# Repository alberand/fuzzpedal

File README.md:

This repository contains a lot of information on how to build a Fuzz Pedal based
on well-known Big Muff PI pedal.

## Demo Reconds

[][4] 

[][5] 

[][6] 

### Schematics

### PCB dimensions

### 3D Render of PCB

### Photo of PCB

### Photo of assembled pedal

## TODO

* Add [rubber feets][1] (After discussion seems to be unnecessary and it's better to have Hook-and-loop fastener)
* Write article on how to paint Aluminum case
* Add template for drilling holes (A4 paper with holes)
* Update BOM (better caps, better LED holder)  - in progress
* Try screen print on the case
* Describe screen printing process
* Find what to use as a final coat for case painting

## Cost

Here is crude cost calculation of one Pedal. Remember that this doesn't include
any tools. The shipping price could vary (in my case I had many more parcels
😕). In total one pedal cost about 50 - 60 💶 euro (without shipping) + you would
have a few paint sprays.

| Material Type                | Quantity       | Price [EUR] |
|------------------------------|----------------|-------------|
| PCB                          | 5 (min amount) |     8.5     |
| Electronic components & Misc |      1 set     |      25     |
| Case                         |        1       |      11     |
| Ground & Color & Clear Paint |        3       |     6x3     |
| Shipping                     |       ~4       |     20x4    |

How long does it take to make a pedal? If you have any experience in soldering,
painting it will take somewhere around 33 hours mainly due waiting for paint to
dry.

| Activity Type             | Time [hours] |
|---------------------------|--------------|
| Board Soldering           |       5      |
| Case drilling             |       2      |
| Case cleaning & polishing |      0.5     |
| Case painting             |      25      |
| Assembling                |      0.5     |

## Assembling process

TODO In progress

The assebmly process is quite simple. The most time-consuming part is PCB
soldering. Otherwise, you just need to put PCB into box.

### Order components & PCB

1. Import BOM to Mouser or Farnell and order components. The BOM is prepared for
   those to distributors. However, sometimes components aren't in stock and it
   can take months for them to restock them.
2. Order the rest of the components from Aliexpress - enclosure and foot switch.
   Those parts are also available on Amazon. I would recommend to by foot switch
   from amazon as it seems to be in better quality. The case could be also
   ordered from Mouser or Farnell.
3. Import Gerber files to PCB manufacturer and order PCBs. I used jlcpcb.com
   which worked out quite well.

### Solder board

1. TODO image of the component placement (print it)
2. I recommend soldering components in the following order:
    1. Resistors
    2. Electrolytic Capacitors (those with polarity)
    3. Capacitor
    4. Transistors
    5. Diodes
    6. Thermal fuse (yellow)
    7. Potentiometers, Jacks and Switch
    8. Wires between PCBs
3. Prepare wires, LED with wires and power jack with wires
4. Solder wires to LED and to the Power jack, but don't solder it to the board
   yet. Also, don't forget to put heat shrink tubes.
5. Solder the LED to the board 

### Enclosure processing

TODO describe what instruments to use
1. Print the template for the hole placement (TODO not in the repo)
2. Cut the template and attach it to the case with adhesive tape
3. Drill the holes
4. Remove the template and polish the case with different sandpapers (TODO add
   sizes)
5. Paint the case (read the instruction on the spray):
    1. 2 layers of primer
    2. 2 layers of color paint
    3. 1 layers of protection layer
6. Screen printing (TODO)

### Assemble the pedal

1. Break the board
2. Put the LED into the case and screw it to the case
3. Screw switch and jacks
4. Put second board into the enclosure and screw the knobs
5. Put power jack into the enclosure
6. Solder power jack wires to the board
7. Use thermal glue (TODO it doesn't work) to fix the board inside the case
8. Screw the bottom of the enclosure

### References

* [ElectroSmash - Big Muff PI analysis](https://www.electrosmash.com/big-muff-pi-analysis)
* [How to "Screen printing"](https://www.youtube.com/watch?v=NS8Q9LUIKA8)

[1]: http://www.diyguitarpedals.com.au/shop/index.php?main_page=product_info&cPath=15&products_id=591
[2]: http://www.caravanelectroworks.com/?p=418
[3]: http://rezzonics.blogspot.com/2018/05/nutube-screamer-schematics-bom-layout.html
[4]: https://soundcloud.com/user-605705068/fuzzpedal-demo-param-1
[5]: https://soundcloud.com/user-605705068/fuzzpedal-demo-param-2
[6]: https://soundcloud.com/user-605705068/fuzzpedal-demo-param-3

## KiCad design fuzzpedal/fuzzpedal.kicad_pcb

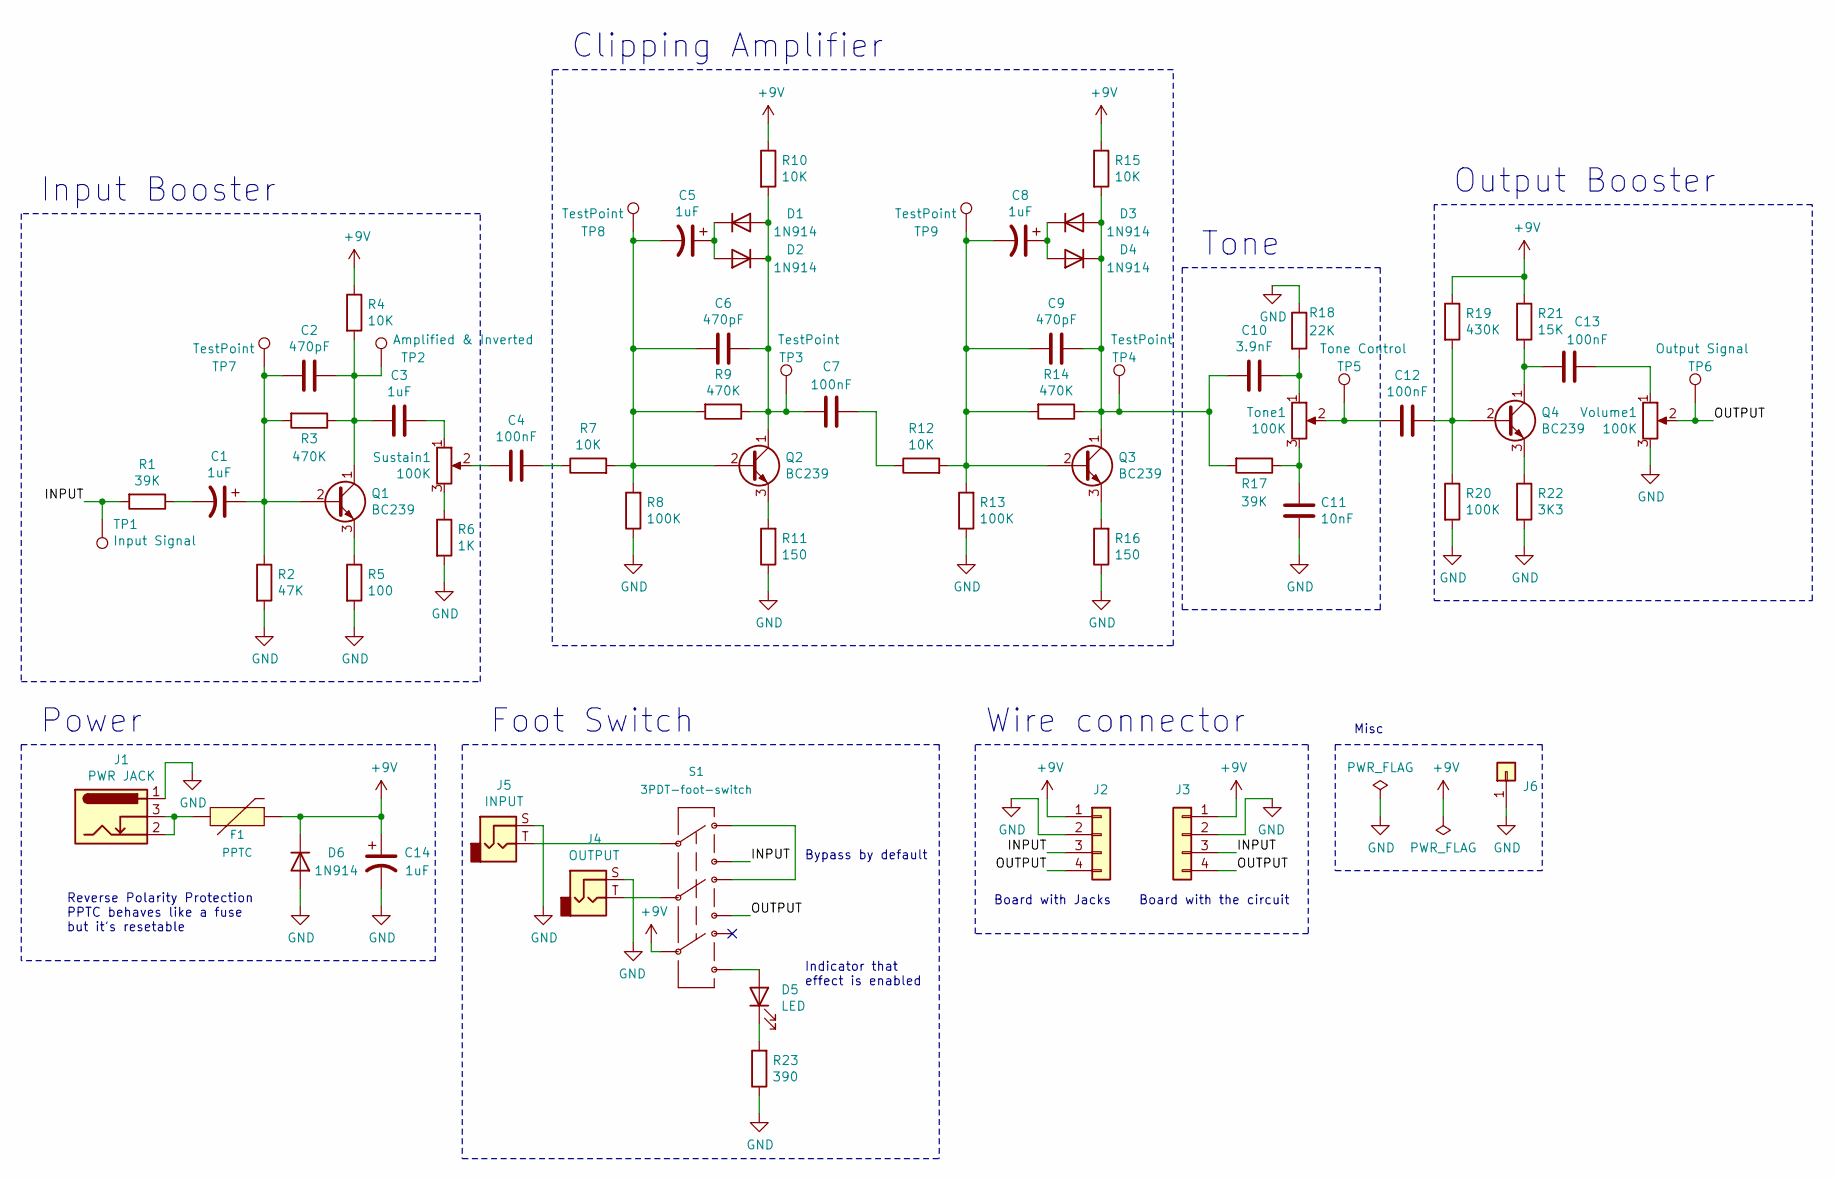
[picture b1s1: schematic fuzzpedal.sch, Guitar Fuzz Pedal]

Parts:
C1, C5, C8, C14: 1uF; CP_Radial_D5.0mm_P2.00mm; Mouser 710-860020672005
C2, C6, C9: 470pF; C_Rect_L7.2mm_W4.5mm_P5.00mm_FKS2_FKP2_MKS2_MKP2; Mouser 505-FKP2D004701DKSSD
C3: 1uF; C_Rect_L7.2mm_W5.5mm_P5.00mm_FKS2_FKP2_MKS2_MKP2; Mouser 505-MKS2C041001FKI00
C4, C7, C12, C13: 100nF; C_Rect_L7.2mm_W2.5mm_P5.00mm_FKS2_FKP2_MKS2_MKP2; Mouser 871-B32529C104K000
C10: 3.9nF; C_Rect_L7.2mm_W4.5mm_P5.00mm_FKS2_FKP2_MKS2_MKP2; Mouser 505-FKP2C013901DHC00
C11: 10nF; C_Rect_L7.2mm_W5.5mm_P5.00mm_FKS2_FKP2_MKS2_MKP2; Mouser 505-FKP2C021001G00KS
D1, D2, D3, D4, D6: 1N914; D_DO-35_SOD27_P7.62mm_Horizontal; LCSC C125665
D5: LED; LED_D5.0mm; LCSC C162069
F1: PPTC; C_Disc_D8.0mm_W2.5mm_P5.00mm; Mouser 652-MF-R020
J1: PWR JACK; PinHeader_1x03_P2.54mm_Vertical
J2: Wire connector (smol); PinHeader_1x04_P2.54mm_Vertical
J3: Wire connector (circuit); PinHeader_1x04_P2.54mm_Vertical
J4: OUTPUT; NMJ6HC-S; Mouser 568-NMJ4HC-S
J5: INPUT; NMJ6HC-S; Mouser 568-NMJ4HC-S
J6: GND for scope; PinHeader_1x01_P2.54mm_Vertical
Q1, Q2, Q3, Q4: BC239; TO-92L_Inline_Wide; Mouser 512-BC549CTA
R1, R17: 39K; R_Axial_DIN0207_L6.3mm_D2.5mm_P10.16mm_Horizontal; Mouser 603-CFR-12JB-52-39K
R2: 47K; R_Axial_DIN0207_L6.3mm_D2.5mm_P10.16mm_Horizontal; Mouser 603-CFR-12JB-52-47K
R3, R9, R14: 470K; R_Axial_DIN0207_L6.3mm_D2.5mm_P10.16mm_Horizontal; Mouser 603-CFR-12JT-52-470K
R4, R7, R10, R12, R15: 10K; R_Axial_DIN0207_L6.3mm_D2.5mm_P10.16mm_Horizontal; Mouser 603-CFR-12JT-52-10K
R5: 100; R_Axial_DIN0207_L6.3mm_D2.5mm_P10.16mm_Horizontal; Mouser 603-CFR-12JT-52-100R
R6: 1K; R_Axial_DIN0207_L6.3mm_D2.5mm_P10.16mm_Horizontal; Mouser 603-CFR-12JT-52-1K
R8, R13, R20: 100K; R_Axial_DIN0207_L6.3mm_D2.5mm_P10.16mm_Horizontal; Mouser 603-CFR-12JR-52-100K
R11, R16: 150; R_Axial_DIN0207_L6.3mm_D2.5mm_P10.16mm_Horizontal; Mouser 603-CFR-12JT-52-150R
R18: 22K; R_Axial_DIN0207_L6.3mm_D2.5mm_P10.16mm_Horizontal; Mouser 603-CFR-12JT-52-22K
R19: 430K; R_Axial_DIN0207_L6.3mm_D2.5mm_P10.16mm_Horizontal; Mouser 603-CFR-12JB-52-430K
R21: 15K; R_Axial_DIN0207_L6.3mm_D2.5mm_P10.16mm_Horizontal; Mouser 603-CFR-12JT-52-15K
R22: 3K3; R_Axial_DIN0207_L6.3mm_D2.5mm_P10.16mm_Horizontal; Mouser 603-CFR-12JR-52-3K3
R23: 390; R_Axial_DIN0207_L6.3mm_D2.5mm_P10.16mm_Horizontal; Mouser 603-CFR-12JB-52-390R
S1: 3PDT-foot-switch; SF17020F-0302-21R-L; Mouser 107-SF17020F-32-21RL
Sustain1: 100K; Potentiometer_Alps_RK09K_Single_Vertical; Mouser 688-RK09D113BF25B15
TP1: Input Signal; TestPoint_Pad_2.0x2.0mm
TP2: Amplified & Inverted; TestPoint_Pad_2.0x2.0mm
TP3, TP4, TP7, TP8, TP9: TestPoint; TestPoint_Pad_2.0x2.0mm
TP5: Tone Control; TestPoint_Pad_2.0x2.0mm
TP6: Output Signal; TestPoint_Pad_2.0x2.0mm
Tone1: 100K; Potentiometer_Alps_RK09K_Single_Vertical; Mouser 688-RK09D113BF25B15
Volume1: 100K; Potentiometer_Alps_RK09K_Single_Vertical; Mouser 688-RK09D113BF25B15

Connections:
+9V: C14.1, D6.1 (K), F1.2, J2.1, J3.1, R4.1, R10.1, R15.1, R19.1, R21.1, S1.8
/INPUT: J2.3, J3.3, R1.2, S1.3, TP1.1
/OUTPUT: J2.4, J3.4, S1.6, TP6.1, Volume1.2
GND: C11.2, C14.2, D6.2 (A), J1.1, J2.2, J3.2, J4.S, J5.S, J6.1, R2.2, R5.2, R6.2, R8.1, R11.1, R13.1, R16.1, R18.1, R20.2, R22.2, R23.1, Volume1.3; also elsewhere on the board
unnamed: C1.1, C2.2, Q1.2 (B), R2.1, R3.2, TP7.1
unnamed: C1.2, R1.1
unnamed: C2.1, C3.2, Q1.1 (C), R3.1, R4.2, TP2.1
unnamed: C3.1, Sustain1.1
unnamed: C4.1, R7.1
unnamed: C4.2, Sustain1.2
unnamed: C5.1, D1.1 (K), D2.2 (A)
unnamed: C5.2, C6.2, Q2.2 (B), R7.2, R8.2, R9.2, TP8.1
unnamed: C6.1, C7.2, D1.2 (A), D2.1 (K), Q2.1 (C), R9.1, R10.2, TP3.1
unnamed: C7.1, R12.1
unnamed: C8.1, D3.1 (K), D4.2 (A)
unnamed: C8.2, C9.2, Q3.2 (B), R12.2, R13.2, R14.2, TP9.1
unnamed: C10.1, R18.2, Tone1.1
unnamed: C9.1, C10.2, D3.2 (A), D4.1 (K), Q3.1 (C), R14.1, R15.2, R17.2, TP4.1
unnamed: C11.1, R17.1, Tone1.3
unnamed: C12.1, Q4.2 (B), R19.2, R20.1
unnamed: C12.2, TP5.1, Tone1.2
unnamed: C13.1, Volume1.1
unnamed: C13.2, Q4.1 (C), R21.2
unnamed: D5.1 (K), R23.2
unnamed: D5.2 (A), S1.9
unnamed: F1.1, J1.2, J1.3
unnamed 26: J4.T, S1.5; also elsewhere on the board
unnamed 27: J5.T, S1.2; also elsewhere on the board
unnamed: Q1.3 (E), R5.1
unnamed: Q2.3 (E), R11.2
unnamed: Q3.3 (E), R16.2
unnamed: Q4.3 (E), R22.1
unnamed: R6.1, Sustain1.3
unnamed: S1.1, S1.4

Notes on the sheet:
Input Booster
Clipping Amplifier
Tone
Output Booster
Bypass by default
Foot Switch
Power
Indicator that effect is enabled
Misc
Reverse Polarity Protection PPTC behaves like a fuse but it's resetable
Board with the circuit
Board with Jacks
Wire connector

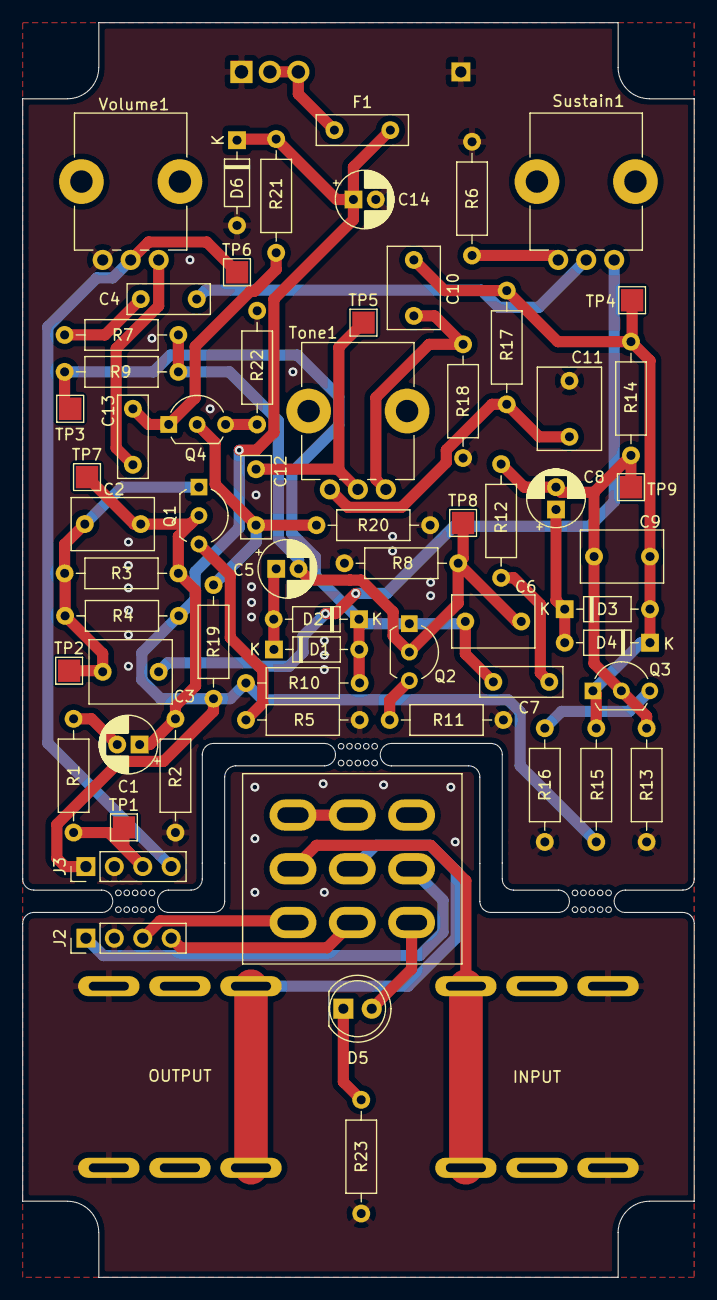
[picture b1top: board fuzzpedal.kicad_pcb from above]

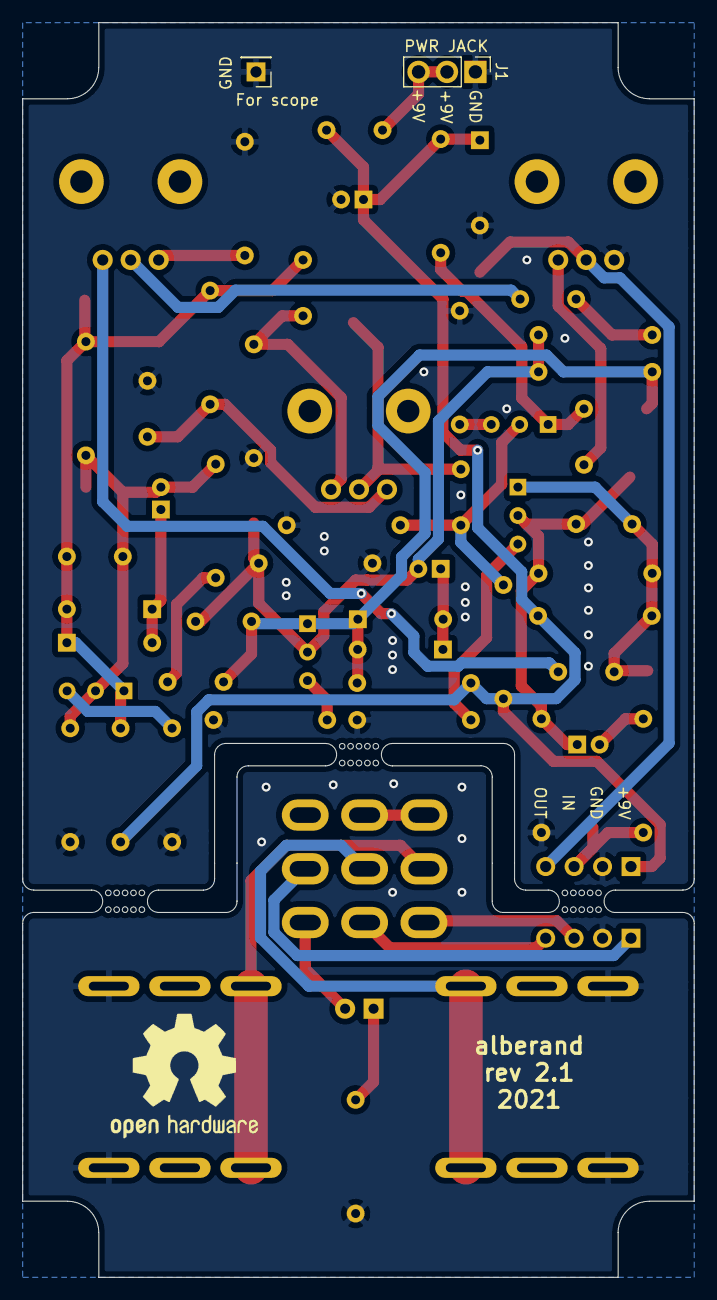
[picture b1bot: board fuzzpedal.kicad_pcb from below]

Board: 2 copper layers, 60.0 x 112.1 mm, 70 parts (2 on the bottom side), 34 nets.

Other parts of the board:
INPUT: INPUT; NMJ6HC-S
Je: GND for scope; PinHeader_1x01_P2.54mm_Vertical
OUTPUT: OUTPUT; NMJ6HC-S
mouse-bite-2mm-slot, mouse-bite-2mm-slot#2, mouse-bite-2mm-slot#3: VAL**; mouse-bite-2mm-slot

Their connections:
GND: INPUT.S, Je.1, OUTPUT.S; also elsewhere on the board
unnamed 26: OUTPUT.T; also elsewhere on the board
unnamed 27: INPUT.T; also elsewhere on the board

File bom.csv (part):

Reference, Value, Footprint, Datasheet, Mfr. No, Mouser, Supplier, LCSC, Aliexpress, Comment, Field4
"R1","39K","Resistor_THT:R_Axial_DIN0207_L6.3mm_D2.5mm_P10.16mm_Horizontal","https://cz.mouser.com/datasheet/2/447/yageo_yagos02873-1-174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","CFR-12JB-52-39K","603-CFR-12JB-52-39K","Mouser","","","",""
"C1","1uF","Capacitor_THT:CP_Radial_D5.0mm_P2.00mm","https://cz.mouser.com/datasheet/2/445/860020672005-1725471.pdf","860020672005","710-860020672005","Mouser","","","",""
"Q1","BC239","Package_TO_SOT_THT:TO-92L_Inline_Wide","https://cz.mouser.com/datasheet/2/308/BC550-D-1802078.pdf","BC549CTA","512-BC549CTA","Mouser","","","",""
"R5","100","Resistor_THT:R_Axial_DIN0207_L6.3mm_D2.5mm_P10.16mm_Horizontal","https://cz.mouser.com/datasheet/2/447/yageo_yagos02873-1-174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","CFR-12JT-52-100R","603-CFR-12JT-52-100R","Mouser","","","",""
"R2","47K","Resistor_THT:R_Axial_DIN0207_L6.3mm_D2.5mm_P10.16mm_Horizontal","https://cz.mouser.com/datasheet/2/447/yageo_yagos02873-1-174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","CFR-12JB-52-47K","603-CFR-12JB-52-47K","Mouser","","","",""
"R3","470K","Resistor_THT:R_Axial_DIN0207_L6.3mm_D2.5mm_P10.16mm_Horizontal","https://cz.mouser.com/datasheet/2/447/yageo_yagos02873-1-174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","CFR-12JT-52-470K","603-CFR-12JT-52-470K","Mouser","","","",""
"C2","470pF","Capacitor_THT:C_Rect_L7.2mm_W4.5mm_P5.00mm_FKS2_FKP2_MKS2_MKP2","https://cz.mouser.com/datasheet/2/440/e_WIMA_FKP_2-1139852.pdf","FKP2D004701D00KSSD ","505-FKP2D004701DKSSD ","Mouser","","","",""
"C3","1uF","Capacitor_THT:C_Rect_L7.2mm_W5.5mm_P5.00mm_FKS2_FKP2_MKS2_MKP2","https://cz.mouser.com/datasheet/2/440/e_WIMA_MKS_2-1139871.pdf","MKS2C041001F00KI00","505-MKS2C041001FKI00","Mouser","","","",""
"R4","10K","Resistor_THT:R_Axial_DIN0207_L6.3mm_D2.5mm_P10.16mm_Horizontal","https://cz.mouser.com/datasheet/2/447/yageo_yagos02873-1-174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","CFR-12JT-52-10K","603-CFR-12JT-52-10K","Mouser","","","",""
"R6","1K","Resistor_THT:R_Axial_DIN0207_L6.3mm_D2.5mm_P10.16mm_Horizontal","https://cz.mouser.com/datasheet/2/447/yageo_yagos02873-1-174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","CFR-12JT-52-1K","603-CFR-12JT-52-1K","Mouser","","","",""
"C4","100nF","Capacitor_THT:C_Rect_L7.2mm_W2.5mm_P5.00mm_FKS2_FKP2_MKS2_MKP2","https://www.tdk-electronics.tdk.com/inf/20/20/db/fc_2009/B32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","B32529C104K000","871-B32529C104K000","Mouser","","","",""
"R7","10K","Resistor_THT:R_Axial_DIN0207_L6.3mm_D2.5mm_P10.16mm_Horizontal","https://cz.mouser.com/datasheet/2/447/yageo_yagos02873-1-174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","CFR-12JT-52-10K","603-CFR-12JT-52-10K","Mouser","","","",""
"Q2","BC239","Package_TO_SOT_THT:TO-92L_Inline_Wide","https://cz.mouser.com/datasheet/2/308/BC550-D-1802078.pdf","BC549CTA","512-BC549CTA","Mouser","","","",""
"R8","100K","Resistor_THT:R_Axial_DIN0207_L6.3mm_D2.5mm_P10.16mm_Horizontal","https://cz.mouser.com/datasheet/2/447/yageo_yagos02873-1-174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","CFR-12JR-52-100K","603-CFR-12JR-52-100K","Mouser","","","",""
"R9","470K","Resistor_THT:R_Axial_DIN0207_L6.3mm_D2.5mm_P10.16mm_Horizontal","https://cz.mouser.com/datasheet/2/447/yageo_yagos02873-1-174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","CFR-12JT-52-470K","603-CFR-12JT-52-470K","Mouser","","","",""
"C6","470pF","Capacitor_THT:C_Rect_L7.2mm_W4.5mm_P5.00mm_FKS2_FKP2_MKS2_MKP2","https://cz.mouser.com/datasheet/2/440/e_WIMA_FKP_2-1139852.pdf","FKP2D004701D00KSSD ","505-FKP2D004701DKSSD ","Mouser","","","",""
"C5","1uF","Capacitor_THT:CP_Radial_D5.0mm_P2.00mm","https://cz.mouser.com/datasheet/2/445/860020672005-1725471.pdf","860020672005","710-860020672005","Mouser","","","",""
"D1","1N914","Diode_THT:D_DO-35_SOD27_P7.62mm_Horizontal","https://cz.mouser.com/datasheet/2/308/1N914-D-1801484.pdf","1N914","512-1N914","Mouser","C125665","","",""
"D2","1N914","Diode_THT:D_DO-35_SOD27_P7.62mm_Horizontal","https://cz.mouser.com/datasheet/2/308/1N914-D-1801484.pdf","1N914","512-1N914","Mouser","C125665","","",""
"R10","10K","Resistor_THT:R_Axial_DIN0207_L6.3mm_D2.5mm_P10.16mm_Horizontal","https://cz.mouser.com/datasheet/2/447/yageo_yagos02873-1-174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","CFR-12JT-52-10K","603-CFR-12JT-52-10K","Mouser","","","",""
"R11","150","Resistor_THT:R_Axial_DIN0207_L6.3mm_D2.5mm_P10.16mm_Horizontal","https://cz.mouser.com/datasheet/2/447/yageo_yagos02873-1-174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","CFR-12JT-52-150R","603-CFR-12JT-52-150R","Mouser","","","",""
"C7","100nF","Capacitor_THT:C_Rect_L7.2mm_W2.5mm_P5.00mm_FKS2_FKP2_MKS2_MKP2","https://www.tdk-electronics.tdk.com/inf/20/20/db/fc_2009/B32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","B32529C104K000","871-B32529C104K000","Mouser","","","",""
"R12","10K","Resistor_THT:R_Axial_DIN0207_L6.3mm_D2.5mm_P10.16mm_Horizontal","https://cz.mouser.com/datasheet/2/447/yageo_yagos02873-1-174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","CFR-12JT-52-10K","603-CFR-12JT-52-10K","Mouser","","","",""
"R13","100K","Resistor_THT:R_Axial_DIN0207_L6.3mm_D2.5mm_P10.16mm_Horizontal","https://cz.mouser.com/datasheet/2/447/yageo_yagos02873-1-174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","CFR-12JR-52-100K","603-CFR-12JR-52-100K","Mouser","","","",""
"R14","470K","Resistor_THT:R_Axial_DIN0207_L6.3mm_D2.5mm_P10.16mm_Horizontal","https://cz.mouser.com/datasheet/2/447/yageo_yagos02873-1-174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","CFR-12JT-52-470K","603-CFR-12JT-52-470K","Mouser","","","",""
"C9","470pF","Capacitor_THT:C_Rect_L7.2mm_W4.5mm_P5.00mm_FKS2_FKP2_MKS2_MKP2","https://cz.mouser.com/datasheet/2/440/e_WIMA_FKP_2-1139852.pdf","FKP2D004701D00KSSD ","505-FKP2D004701DKSSD ","Mouser","","","",""
"C8","1uF","Capacitor_THT:CP_Radial_D5.0mm_P2.00mm","https://cz.mouser.com/datasheet/2/445/860020672005-1725471.pdf","860020672005","710-860020672005","Mouser","","","",""
"D3","1N914","Diode_THT:D_DO-35_SOD27_P7.62mm_Horizontal","https://cz.mouser.com/datasheet/2/308/1N914-D-1801484.pdf","1N914","512-1N914","Mouser","C125665","","",""
"D4","1N914","Diode_THT:D_DO-35_SOD27_P7.62mm_Horizontal","https://cz.mouser.com/datasheet/2/308/1N914-D-1801484.pdf","1N914","512-1N914","Mouser","C125665","","",""
"R15","10K","Resistor_THT:R_Axial_DIN0207_L6.3mm_D2.5mm_P10.16mm_Horizontal","https://cz.mouser.com/datasheet/2/447/yageo_yagos02873-1-174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","CFR-12JT-52-10K","603-CFR-12JT-52-10K","Mouser","","","",""
"R16","150","Resistor_THT:R_Axial_DIN0207_L6.3mm_D2.5mm_P10.16mm_Horizontal","https://cz.mouser.com/datasheet/2/447/yageo_yagos02873-1-174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","CFR-12JT-52-150R","603-CFR-12JT-52-150R","Mouser","","","",""
"Tone1","100K","Potentiometer_THT:Potentiometer_Alps_RK09K_Single_Vertical","https://cz.mouser.com/datasheet/2/15/RK09K-771158.pdf","RK09D113BF25B15","688-RK09D113BF25B15","Mouser","","","",""
"C10","3.9nF","Capacitor_THT:C_Rect_L7.2mm_W4.5mm_P5.00mm_FKS2_FKP2_MKS2_MKP2","https://cz.mouser.com/datasheet/2/440/e_WIMA_FKP_2-1139852.pdf","FKP2C013901D00HC00","505-FKP2C013901DHC00","Mouser","","","",""
"R17","39K","Resistor_THT:R_Axial_DIN0207_L6.3mm_D2.5mm_P10.16mm_Horizontal","https://cz.mouser.com/datasheet/2/447/yageo_yagos02873-1-174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","CFR-12JB-52-39K","603-CFR-12JB-52-39K","Mouser","","","",""
"R18","22K","Resistor_THT:R_Axial_DIN0207_L6.3mm_D2.5mm_P10.16mm_Horizontal","https://cz.mouser.com/datasheet/2/447/yageo_yagos02873-1-174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","CFR-12JT-52-22K ","603-CFR-12JT-52-22K ","Mouser","","","",""
"C12","100nF","Capacitor_THT:C_Rect_L7.2mm_W2.5mm_P5.00mm_FKS2_FKP2_MKS2_MKP2","https://www.tdk-electronics.tdk.com/inf/20/20/db/fc_2009/B32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","B32529C104K000","871-B32529C104K000","Mouser","","","",""
"Q4","BC239","Package_TO_SOT_THT:TO-92L_Inline_Wide","https://cz.mouser.com/datasheet/2/308/BC550-D-1802078.pdf","BC549CTA","512-BC549CTA","Mouser","","","",""
"R21","15K","Resistor_THT:R_Axial_DIN0207_L6.3mm_D2.5mm_P10.16mm_Horizontal","https://cz.mouser.com/datasheet/2/447/yageo_yagos02873-1-174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","CFR-12JT-52-15K","603-CFR-12JT-52-15K","Mouser","","","",""
"R19","430K","Resistor_THT:R_Axial_DIN0207_L6.3mm_D2.5mm_P10.16mm_Horizontal","https://cz.mouser.com/datasheet/2/447/yageo_yagos02873-1-174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","CFR-12JB-52-430K","603-CFR-12JB-52-430K","Mouser","","","",""
"C13","100nF","Capacitor_THT:C_Rect_L7.2mm_W2.5mm_P5.00mm_FKS2_FKP2_MKS2_MKP2","https://www.tdk-electronics.tdk.com/inf/20/20/db/fc_2009/B32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","B32529C104K000","871-B32529C104K000","Mouser","","","",""
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
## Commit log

2020-05-09 add: initial schematics
2020-05-09 add: README.md
2020-05-10 add: not connected to switch
2020-05-10 add: assign big bunch of components
2020-05-10 add: gitattributes for lfs
2020-05-10 add: datasheets
2020-05-22 fix: audio IN/OUT change to 4 pin jacks
2020-05-22 add: footprints for 100SP switch and 3PDT foot switch
2020-05-22 add: other minor hw changes
2020-05-22 add: more datasheets
2020-06-09 add: 3D models for component
2020-06-09 add: footprint for NMJ6HC-S
2020-06-09 add: mostly hw layout
2020-06-09 add: some notes to readme
2020-06-09 add: dir for mechanics
2020-06-09 fix: more changes to the layout
2020-06-10 fix: update capacitors to the Film one
2020-06-11 fix: re-layout board for a new film capacitors
2020-06-11 fix: 3D models of capacitors and wire buses
2020-06-20 add: layout changes
2020-06-20 fix: LED indicates effect
2020-06-20 fix: new LED position on the board
    As now LED is used to indicate enabled effect it should be located near the foot switch
2020-06-20 fix: remove 3D models from pin headers
2020-06-20 fix: silk screen
2020-06-21 add: images to README
2020-06-22 fix: LED shows when effect is on
2020-06-22 refactor: remove old BOM
2020-06-22 add: slight changes in bom
2020-06-22 fix: wrong input resistor
2020-06-22 fix: reroute board for LED
2020-06-23 add: OSHW and sing silkscreen
2020-06-23 fix: some minor silkscreen
2020-06-24 add: gerbers for rev 1.0
2020-06-24 add: gerber output directory
2020-06-24 fix: wrong resistor value
2020-06-24 add: BOM for rev 1.0
2020-06-24 fix: cut off schematics image
2020-06-24 fix: rename and enlarge PCB render image
2020-06-24 fix: change resistor model
    On the previous one min. order is 5000 pieces
2020-06-25 fix: too small spacing (3 mm min)
2020-06-25 add: new gerbers with bigger spacing
2020-07-24 fix: adjust size of the board to 1590N1
2020-07-24 add: dimension notation on PCB
2020-07-24 add: PCB images
2020-07-24 fix: update schematics
2020-08-12 add: redo board cut off for new board
2020-08-12 add: PCB 3d model
2020-08-12 fix: wide footprint for transistors
2020-08-13 add: reverse polarity protection based on PPTC
2020-08-13 add: notes to README
2020-08-13 add: more testpoints
2020-08-13 fix: change revision number to two
2020-08-13 add: assign footprint to PPTC
2020-08-13 fix: minor name fix for PPTC
2020-08-13 fix: regenerate netlist
2020-08-13 add: pick PPTC component on mouser
2020-08-13 fix: wider pads for 3PDT foot switch
2020-08-14 add: decoupling transistor
2020-08-14 add: update netlist to rev 2.0
2020-08-14 fix: switch input and output jacks
2020-08-14 refactor: remove tracks, mouse bites, fab text
2020-08-14 add: GND pin for scope
2020-08-14 add: note about enclosure painting
2020-08-14 add: skeleton of the assembling manual
2020-08-14 fix: transistor pin mapping
2020-08-25 add: wire connectors on schematics
2020-08-25 add: layout testpoints
2020-08-25 fix: wrong footprint for connectors
2020-08-28 add: first version of new layout
2020-08-29 fix: increase size of the pads for jacks and footswitch
2020-08-29 fix: update footprints on the board
2020-08-29 add: link to video about screen printing
2020-08-29 fix: assign 3D models to footprints
2020-08-29 add: dimensions + minor fixes
2020-08-29 add: reason why board is divided into two
2020-08-29 fix: one of the dimensions
2020-08-29 fix: bigger pads for barell jack
2020-08-29 fix: minor fixes of vias and page settings
2020-08-29 add: new gerbers
2020-08-29 fix: minor fixes
2020-08-29 refactor: remove pin header 3D model
2020-08-29 add: new images
2020-08-29 add: new BOM
2020-09-09 fix: silkscreen with rev2.0
2020-09-09 refactor: changed notes
2020-09-09 fix: misc
2020-09-18 add: the latest gerbers for v2.0
2020-09-30 add: Interactive BOM
2020-09-30 add: photo of PCB
2020-09-30 fix: wrong photo format
2020-10-24 add: photos of assembled pedal
2020-10-24 fix: wrong photo extension
2020-10-24 fix: adjust hue on some photos
2020-10-24 fix: photo extension
2020-10-24 refactor: update readme
2020-10-24 docs: more TODOs in readme
2020-10-28 fix: remove grey borders on photos
2020-10-28 add: cost & time calculation
2020-10-28 fix: more EMOJI
2020-10-28 refactor: rename hardware dir
2020-10-28 refactor: more renaming
2021-01-07 refactor: a lot of renaming
2021-01-07 refactor: just a minor metadata fixes
2021-01-07 fix: increase hole size for the foot switch
2021-01-07 fix: hole sizes of the jacks + bigger OSHW logo
2021-01-07 add: kicad temp files to gitignore
2021-01-07 refactor: remove unused mechanical dir
2021-01-07 add: newly generated gerbers
2021-01-07 add: hw revision version to 2.1
2021-02-06 add: better structure and description of assembly process
2021-04-02 add: demo configurations
2021-04-02 add: table with demos
2021-04-02 add: header to the demo table
2021-04-02 test: better demos layout
2021-04-02 test: wide image with link for demo
2021-04-02 add: demo3 wide image
2021-04-02 test: demo links
2021-04-02 fix: narrow demo3
2021-04-02 add: new demo images
2021-04-02 doc: move demos up
